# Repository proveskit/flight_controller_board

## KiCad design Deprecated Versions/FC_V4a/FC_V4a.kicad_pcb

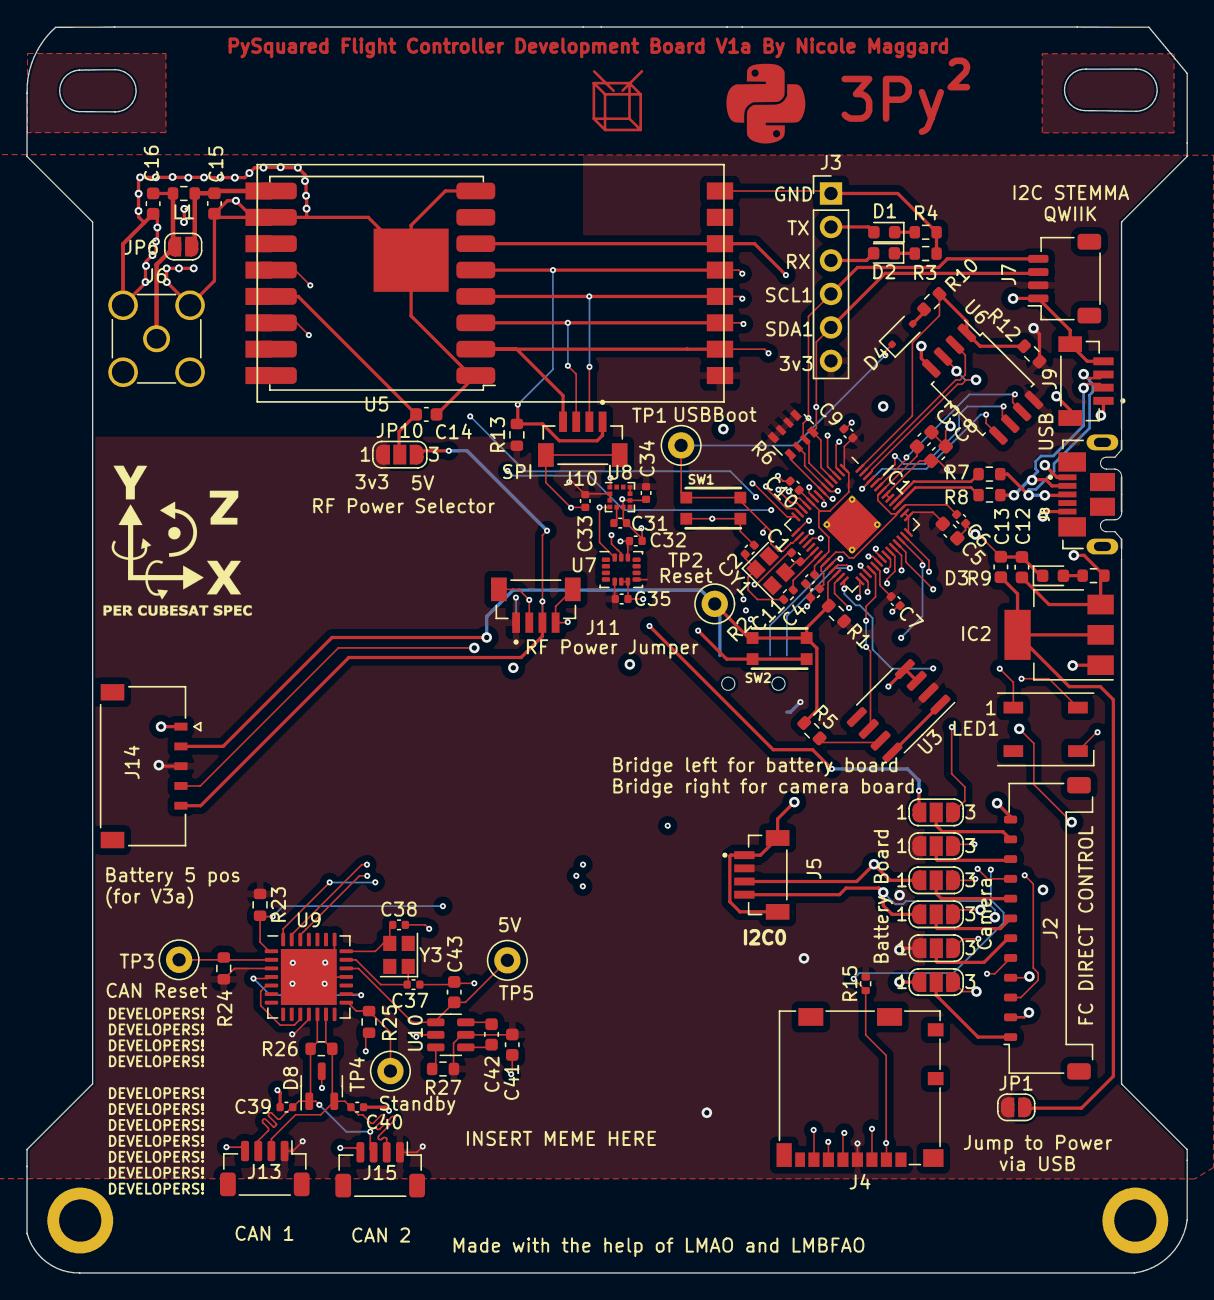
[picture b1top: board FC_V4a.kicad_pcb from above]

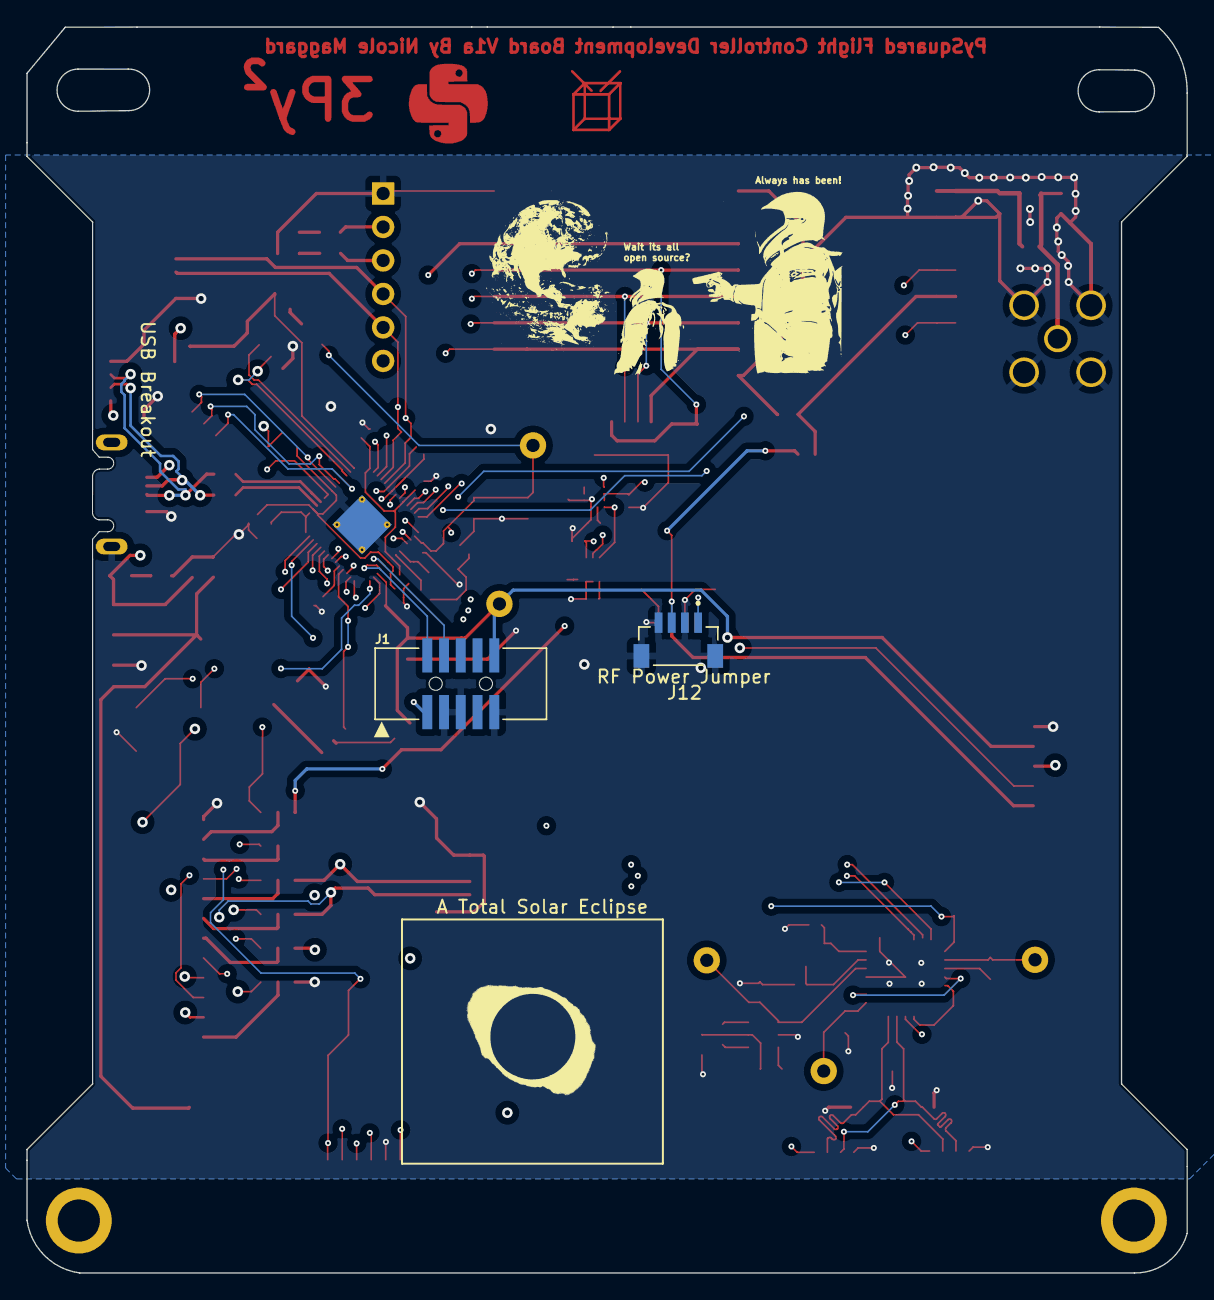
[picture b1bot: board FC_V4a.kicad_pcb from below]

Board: 4 copper layers, 88.0 x 94.5 mm, 96 parts (2 on the bottom side), 80 nets.

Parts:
C1, C2: 22pF; C_0402_1005Metric
C3, C6, C8: 1uF; C_0603_1608Metric
C4, C5, C7, C9, C10, C11, C32, C33, C34, C35: 100nf; C_0402_1005Metric
C12, C14: 10uF; C_0603_1608Metric
C13: 22uF; C_0603_1608Metric
C15, C16: DNI; C_0603_1608Metric
C31: 220nf; C_0402_1005Metric
C37, C38: 22pf; C_0402_1005Metric
C39, C40: 47pf; C_0402_1005Metric
C41, C43: 10uf; C_0603_1608Metric
C42: 1uf; C_0603_1608Metric
D1, D2, D3: LED; LED_0603_1608Metric
D4: NSR0320; D_SOD-323F
D8: PESD1CAN; SOT-23-3
IC1: RP2040_QFN56; QFN-56-1EP_7x7mm_P0.4mm_EP3.2x3.2mm_ThermalVias
IC2: AZ1117CH-3.3TRG1; SOT-223
J1: Conn_ARM_JTAG_SWD_10; JTAG_2X05_1.27MM_BOX_NOCREAM
J2: FC to EPS Connector; Molex_Pico-Lock_504050-1291_1x12-1MP_P1.50mm_Horizontal
J3: DNI; PinHeader_1x06_P2.54mm_Vertical
J4: 104031-0811; microSD_HC_Molex_104031-0811
J5, J9, J10, J11, J12: BM04B-SRSS-TB(LF)(SN); JST_BM04B-SRSS-TB(LF)(SN)
J6: Conn_Coaxial; SMA_Amphenol_901-144_Vertical
J7: Breakout; JST_SH_SM04B-SRSS-TB_1x04-1MP_P1.00mm_Horizontal
J8: USB_B_Micro; MOLEX_105164-0001
J13, J15: Breakout; JST_SH_BM04B-SRSS-TB_1x04-1MP_P1.00mm_Vertical
J14: Battery; MOLEX_5040500591
JP1, JP6: SolderJumper_2_Open; SolderJumper-2_P1.3mm_Open_RoundedPad1.0x1.5mm
JP3, JP4, JP5, JP7, JP8, JP9, JP10: Jumper_3_Open; SolderJumper-3_P1.3mm_Open_RoundedPad1.0x1.5mm_NumberLabels
L1: DNI; R_0603_1608Metric
LED1: WS2812B_SK6812_1515; LED_WS2812B_PLCC4_5.0x5.0mm_P3.2mm
R1, R5, R9, R12, R13, R23, R24, R25, R27: 10k; R_0603_1608Metric
R2: 1k; R_0402_1005Metric
R3, R4, R10: 1k; R_0603_1608Metric
R6: 10k; R_Array_Convex_4x0603
R7, R8: 22; R_0603_1608Metric
R15: 10k; R_0402_1005Metric
R26: 120; R_0603_1608Metric
SW1, SW2: KMR2; BTN_KMR2_4.6X2.8
TP1: USBBOOT; TestPoint_Loop_D1.80mm_Drill1.0mm_Beaded
TP2, TP3: RESET; TestPoint_Loop_D1.80mm_Drill1.0mm_Beaded
TP4: Standby; TestPoint_Loop_D1.80mm_Drill1.0mm_Beaded
TP5: 5V; TestPoint_Loop_D1.80mm_Drill1.0mm_Beaded
U3: MAX706RESA; SO-8_3.9x4.9mm_P1.27mm
U4: RFM98PW
U5: RFM9xBreakout; HOPERF_RFM9XW_SMD
U6: W25Q128JV; SOIC-8_5.275x5.275mm_P1.27mm
U7: LSM6DSOTR; LGA-14_3x2.5mm_P0.5mm_LayoutBorder3x4y
U8: LSM303AGRTR; LGA-12_2x2mm_P0.5mm
U9: MCP25625-E/ML; QFN-28-1EP_6x6mm_P0.65mm_EP4.25x4.25mm
U10: AP3602AKTR-G1; SOT-23-6
Y1: 12MHZ; Crystal_SMD_2520-4Pin_2.5x2.0mm
Y3: 16MHZ 12 pf; Crystal_SMD_2520-4Pin_2.5x2.0mm

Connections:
1.2V: C3.1, C4.2, C5.2, IC1.23 (DVDD), IC1.45 (VREG_VOUT), IC1.50 (DVDD)
3.3V: C6.1, C7.1, C8.1, C9.1, C10.1, C11.1, C32.1, C33.1, C34.1, C35.1, C41.2, IC1.1 (IOVDD), IC1.10 (IOVDD), IC1.22 (IOVDD), IC1.33 (IOVDD), IC1.42 (IOVDD), IC1.43 (ADC_IOVDD), IC1.44 (VREG_IOVDD), IC1.48 (USB_IOVDD), IC1.49 (IOVDD), J1.1 (VTref), J3.6, J4.4 (VDD), J5.2, J7.2, J11.1, J12.1, J13.1, J14.3, J15.1, JP1.1 (A), JP4.1 (A), JP5.1 (A), JP10.1 (A), R1.1, R6.5 (R4.2), R6.6 (R3.2), R6.7 (R2.2), R6.8 (R1.2), R12.1, R13.1, R15.2, R23.1, R24.1, R27.1, U3.2 (VCC), U4.9 (3.3V), U6.8 (VCC), U7.5 (VDDIO), U7.8 (VDD), U7.12 (CS), U8.2 (CS_XL), U8.3 (CS_MAG), U8.9 (VDD), U8.10 (VDD_IO), U9.3 (VDD@1), U9.11 (VIO), U10.5 (VIN)
+5V: C43.2, TP5.1, U9.19 (VDDA), U10.1 (VOUT)
/3v3 Spec: C13.1, IC2.2 (OUTPUT), IC2.4 (VOUT), JP1.2 (B)
/D+: IC1.47 (USB_D+), R7.1
/D-: IC1.46 (USB_D-), R8.1
/QSPI_CS: IC1.56 (~QSPI_CS), R10.1, R12.2, U6.1 (SSEL)
/QSPI_DATA[0]: IC1.53 (QSPI_SD0), U6.5 (MOSI)
/QSPI_DATA[1]: IC1.55 (QSPI_SD1), U6.2 (MISO)
/QSPI_DATA[2]: IC1.54 (QSPI_SD2), U6.3 (WP#/IO2)
/QSPI_DATA[3]: IC1.51 (QSPI_SD3), U6.7 (HOLD#/IO3)
/QSPI_SCK: IC1.52 (QSPI_SCLK), U6.6 (SCK)
BURN_RELAY_A / D5: IC1.18 (GPIO15), JP9.3 (B)
CANH: C40.2, D8.2, J13.2, J15.2, R26.2, U9.13 (CANH)
CANL: C39.1, D8.1, J13.3, J15.3, R26.1, U9.12 (CANL)
D0: IC1.41 (GPIO29/AD3), J14.4
D3: D4.1 (K), IC1.16 (GPIO13), J2.5, SW1.A, SW1.A' (P1), TP1.1
D6: IC1.27 (GPIO16), JP8.3 (B)
D7: IC1.28 (GPIO17), J2.9
D8: IC1.29 (GPIO18), JP5.3 (B)
D9: IC1.30 (GPIO19), JP7.3 (B)
ENABLE_BURN / PC: IC1.8 (GPIO6), J2.3
ENAB_RF / D2: IC1.15 (GPIO12), J2.4
FC_RESET: IC1.26 (/RUN), J1.10 (~RESET), J14.2, R1.2, R5.1, SW2.A, SW2.A' (P1), TP2.1
GND: C1.1, C2.1, C3.2, C4.1, C5.1, C6.2, C7.2, C8.2, C9.2, C10.2, C11.2, C12.2, C13.2, C14.1, C15.2, C16.2, C31.2, C32.2, C33.2, C34.2, C35.2, C37.2, C38.2, C39.2, C40.1, C41.1, C43.1, D3.1 (K), D8.3, IC1.57 (GND), IC2.1 (ADJ/GND), J1.3 (GND), J1.5 (GND), J1.9 (GNDDetect), J2.12, J3.1, J4.6 (VSS), J5.1, J5.S1 (SHIELD), J5.S2 (SHIELD), J6.2 (Ext), J7.1, J8.5 (GND), J8.SH1 (Shield), J9.4, J9.S1 (SHIELD), J9.S2 (SHIELD), J10.S1 (SHIELD), J10.S2 (SHIELD), J11.2, J11.4, J11.S1 (SHIELD), J11.S2 (SHIELD), J12.2, J12.4, J12.S1 (SHIELD), J12.S2 (SHIELD), J13.4, J14.1, J15.4, JP3.1 (A), LED1.3 (GND), R3.2, R4.2, R25.1, SW1.B (S), SW1.B' (S1), SW2.B (S), SW2.B' (S1), U3.3 (GND), U3.4 (PFI), U4.2 (GND), U4.16 (GND), U4.17 (GND), U5.1 (GND), U5.8 (GND), U5.10 (GND), U6.4 (VSS), U7.6 (GND), U7.7 (GND), U8.6 (GND), U8.8 (GND), U9.18 (VSS@1), U9.22 (GND), U9.29 (GND@1), U10.2 (GND)
HS: IC1.37 (GPIO25), JP3.3 (B)
I2C_RESET / VS: IC1.9 (GPIO7), J2.2
NEOPIX: IC1.36 (GPIO24), LED1.4 (DI)
Neo_pwr: IC1.39 (GPIO27/AD1), LED1.1 (VDD)
unnamed: C2.2, R2.2, Y1.1
unnamed: D1.1 (K), R4.1
unnamed: D2.1 (K), R3.1
unnamed: D3.2 (A), R9.2
unnamed: D4.2 (A), R10.2
unnamed: C1.2, IC1.20 (XIN), Y1.3 (2)
unnamed: IC1.21 (XOUT), R2.1
unnamed: J2.1, JP3.2 (C)
unnamed: J2.6, JP4.2 (C)
unnamed: J2.7, JP9.2 (C)
unnamed: J2.8, JP8.2 (C)
unnamed: J2.10, JP5.2 (C)
unnamed: J2.11, JP7.2 (C)
unnamed: C16.1, J6.1 (In), JP6.1 (A), L1.2
unnamed: U3.1 (~MR), U3.8 (~WDO)
unnamed: R5.2, U3.7 (~RESET)
unnamed: C31.1, U8.5 (C1)
unnamed: C38.1, U9.21 (OSC1), Y3.3 (2)
unnamed: C37.1, U9.20 (OSC2), Y3.1
unnamed: R24.2, TP3.1, U9.2 (RESET)
unnamed: R25.2, TP4.1, U9.15 (STBY)
unnamed: R27.2, U10.3 (*SHDN)
unnamed: C42.2, U10.6 (C+)
unnamed: C42.1, U10.4 (C-)
RF1_ANT: C15.1, JP6.2 (B), L1.1, U4.1 (ANT), U5.9 (ANT)
RF1_IO0: IC1.35 (GPIO23), U4.6 (GPIO_0), U5.14 (DIO0)
RF1_IO4: IC1.34 (GPIO22), U4.4 (GPIO_4), U5.12 (BUSY)
RF1_RST: IC1.31 (GPIO20), U4.14 (RESET), U5.6 (~RESET)
RF_VCC: C14.2, JP10.2 (C), U4.5 (VCC), U5.13 (3V3)
RX: D2.2 (A), IC1.3 (GPIO1), J3.3
RXCAN: U9.5 (RXCAN), U9.10 (RXD)
SCL0: IC1.7 (GPIO5), J5.4, JP9.1 (A), R6.1 (R1.1)
SCL1: IC1.5 (GPIO3), J3.4, J7.4, R6.3 (R3.1), U7.13 (SCL), U8.1 (SCL/SPC)
SDA0: IC1.6 (GPIO4), J5.3, JP8.1 (A), R6.2 (R2.1)
SDA1: IC1.4 (GPIO2), J3.5, J7.3, R6.4 (R4.1), U7.14 (SDA), U8.4 (SDA/SDI/SDO)
SPI0_CS0: IC1.12 (GPIO9), J10.1, R13.2, U4.13 (NSS), U5.5 (CS)
SPI0_CS1: IC1.38 (GPIO26/AD0), J4.2 (CD/DAT3), R15.1
SPI0_CS2: IC1.40 (GPIO28/AD2), R23.2, U9.1 (CS)
SPI0_MISO: IC1.11 (GPIO8), J4.7 (DAT0), J10.4, U4.10 (MISO), U5.2 (MISO), U9.28 (SO)
SPI0_MOSI: IC1.14 (GPIO11), J4.3 (CMD), J10.3, U4.11 (MOSI), U5.3 (MOSI), U9.27 (SI)
SPI0_SCK: IC1.13 (GPIO10), J4.5 (CLK), J10.2, U4.12 (SCK), U5.4 (SCK), U9.26 (SCK)
SWCLK: IC1.24 (SWCLK), J1.4 (SWDCLK/TCK)
SWDIO: IC1.25 (SWDIO), J1.2 (SWDIO/TMS)
TX: D1.2 (A), IC1.2 (GPIO0), J3.2
TXCAN: U9.4 (TXCAN), U9.16 (TXD)
USB_D+: J8.3 (D+), J9.3, R7.2
USB_D-: J8.2 (D-), J9.2, R8.2
VBUS: C12.1, IC2.3 (INPUT), J8.1 (VBUS), J9.1, R9.1
VBUS_RESET / D4: IC1.17 (GPIO14), JP4.3 (B)
VCC_RF1: J11.3, J12.3, J14.5, JP7.1 (A), JP10.3 (B)
WDT_WDI: IC1.32 (GPIO21), U3.6 (~WDI)
